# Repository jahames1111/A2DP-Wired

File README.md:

## A2DP-Wired headphones adapter

# Idea:

My parents are, well, old, so they have a lot of old wired headphones lying around their house. However, most of these are useless as their phones don't have the right kind of audio connector. I built this project to let them use all of their wired headphones with Bluetooth so they don't have to throw them away. This combines the best and easiest-to-solder chips that I could possibly find to make a device that turns these old pieces of hardware into useful music streaming tools.

Portable Bluetooth wired headphones adapter.

# Features

• ESP32-WROOM-32E: Bluetooth classic streaming

• PCM5102A DAC: audio 

• SSD1306 OLED: status screen

• 5V USB-C / LiPo: power

• SPDT Switch: Power input switching

• MIC5219 LDO: holds 3V3

• CH340C Serial: Easy USB programming

• 0805 Footprints: Hand-solder friendly

# Onboard Parts & Connectors

|Designators        |Value                    |Package  |LCSC#    |MPN                |Manufacturer             |
|-------------------|-------------------------|---------|---------|-------------------|-------------------------|
|C1                 |10uF                     |0603     |C19702   |CL10A106KP8NNNC    |Samsung Electro-Mechanics|
|C2                 |470pF                    |0603     |C22396   |CL10B471KB8NNNC    |Samsung Electro-Mechanics|
|C3                 |10uF                     |0805     |C440198  |GRM21BR61H106KE43L |muRata                   |
|C4,C5,C6,C9        |100nF                    |0603     |C1591    |CL10B104KB8NNNC    |Samsung Electro-Mechanics|
|C7,C8              |2.2uF                    |0805     |C19110   |CL21B225KAFNNNE    |Samsung Electro-Mechanics|
|C10,C11            |2.2nF                    |0603     |C16033   |CL10B222KB8NNNC    |Samsung Electro-Mechanics|
|R1,R2              |5.1k                     |0603     |C2907044 |FRC0603F5101TS     |FOJAN                    |
|R3,R4              |10k                      |0603     |C98220   |RC0603FR-0710KL    |YAGEO                    |
|R5                 |330                      |0603     |C23138   |0603WAF3300T5E     |UNI-ROYAL                |
|R6                 |2k                       |0603     |C22975   |0603WAF2001T5E     |UNI-ROYAL                |
|R7,R10             |470                      |0603     |C23179   |0603WAF4700T5E     |UNI-ROYAL                |
|R8,R9              |100k                     |0603     |C14675   |RC0603FR-07100KL   |YAGEO                    |
|R11,R12            |4.7k                     |0603     |C99782   |RC0603FR-074K7L    |YAGEO                    |
|D1                 |LED Red                  |0603     |C2286    |KT-0603R           |Hubei KENTO              |
|U1                 |ESP32-WROOM-32E-N16      |Module   |C701343  |ESP32-WROOM-32E-N16|ESPRESSIF                |
|U2                 |CH340C                   |SOP-16   |C84681   |CH340C             |WCH                      |
|U3                 |MIC5219-3.3YM5 Compatible|SOT-23-5L|C41381680|HMIC5219-3.3YM5    |HXY                      |
|U4                 |MCP73831T-2ACI/OT        |SOT-23-5 |C424093  |MCP73831T-2ACI/OT  |MICROCHIP                |
|U5                 |PCM5102APW               |TSSOP-20 |C1520792 |PCM5102APW         |TI                       |
|J1                 |USB-C Receptacle         |SMD      |C165948  |TYPE-C-31-M-12     |Hroparts                 |
|J4                 |3.5mm Audio Jack         |SMD      |C431535  |PJ-320D            |SHOU HAN                 |
|SW1,SW2            |Tactile Switch           |SMD      |C2886894 |TL3342F260QG       |E-Switch                 |
|SW3                |Slide Switch SPDT        |SMD      |C221841  |PCM12SMTR          |C&K                      |
|SW4,SW5,SW6,SW7,SW8|Tactile Switch           |THT      |C393938  |TS665CJ            |SHOU HAN                 |

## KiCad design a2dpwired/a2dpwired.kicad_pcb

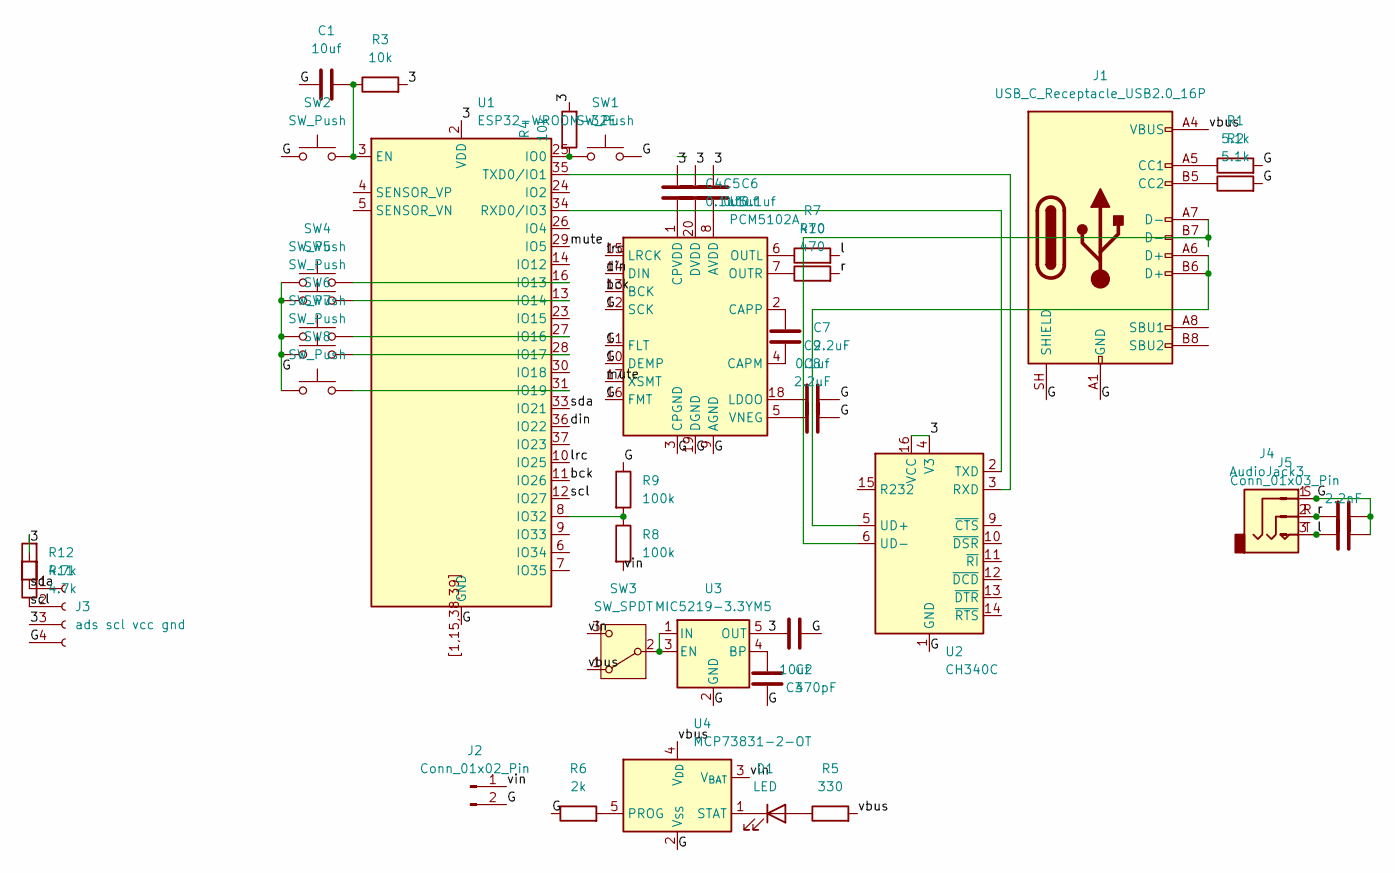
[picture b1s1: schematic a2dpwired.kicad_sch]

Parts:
C1: 10uf; C_0603_1608Metric_Pad1.08x0.95mm_HandSolder
C2: 470pF; C_0603_1608Metric_Pad1.08x0.95mm_HandSolder
C3: 10uf; C_0805_2012Metric_Pad1.18x1.45mm_HandSolder
C4, C5, C6, C9: 0.1uf; C_0603_1608Metric_Pad1.08x0.95mm_HandSolder
C7, C8: 2.2uF; C_0805_2012Metric_Pad1.18x1.45mm_HandSolder
C10, C11: 2.2nF; C_0603_1608Metric_Pad1.08x0.95mm_HandSolder
D1: LED; LED_0805_2012Metric_Pad1.15x1.40mm_HandSolder
J1: USB_C_Receptacle_USB2.0_16P; USB_C_Receptacle_HRO_TYPE-C-31-M-12
J2: Conn_01x02_Pin; PinSocket_1x02_P2.54mm_Vertical
J3: ads scl vcc gnd; PinSocket_1x04_P2.54mm_Vertical
J4: AudioJack3; Jack_3.5mm_PJ320D_Horizontal
J5: Conn_01x03_Pin; PinSocket_1x03_P2.54mm_Vertical
R1, R2: 5.1k; R_0603_1608Metric_Pad0.98x0.95mm_HandSolder
R3, R4: 10k; R_0603_1608Metric_Pad0.98x0.95mm_HandSolder
R5: 330; R_0603_1608Metric_Pad0.98x0.95mm_HandSolder
R6: 2k; R_0603_1608Metric_Pad0.98x0.95mm_HandSolder
R7, R10: 470; R_0603_1608Metric_Pad0.98x0.95mm_HandSolder
R8, R9: 100k; R_0603_1608Metric_Pad0.98x0.95mm_HandSolder
R11, R12: 4.7k; R_0603_1608Metric_Pad0.98x0.95mm_HandSolder
SW1, SW2: SW_Push; SW_SPST_TL3342
SW3: SW_SPDT; SW_SPDT_PCM12
SW4, SW5, SW6, SW7, SW8: SW_Push; SW_PUSH_6mm_H4.3mm
U1: ESP32-WROOM-32E
U2: CH340C; SOIC-16_3.9x9.9mm_P1.27mm
U3: MIC5219-3.3YM5; SOT-23-5
U4: MCP73831-2-OT; SOT-23-5
U5: PCM5102A; TSSOP-20_4.4x6.5mm_P0.65mm

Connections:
/3: C3.2, C4.1, C5.1, C6.1, J3.3, R3.2, R4.2, R11.2, R12.2, U1.2 (VDD), U2.4 (V3), U2.16 (VCC), U3.5 (OUT)
/G: C1.1, C2.2, C3.1, C8.2, C9.2, C10.2, C11.2, J1.A1 (GND), J1.A12 (GND), J1.B1 (GND), J1.B12 (GND), J1.SH (SHIELD), J2.2, J3.4, J4.S, J5.1, R1.2, R2.2, R6.1, R9.1, SW1.2, SW2.1, SW4.1, SW5.1, SW6.1, SW7.1, SW8.1, U1.1 (GND), U1.15 (GND), U1.38 (GND), U1.39 (GND), U1.[1,15,38,39] (GND), U2.1 (GND), U3.2 (GND), U4.2 (V_{SS}), U5.3 (CPGND), U5.9 (AGND), U5.10 (DEMP), U5.11 (FLT), U5.12 (SCK), U5.16 (FMT), U5.19 (DGND)
/bck: U1.11 (IO26), U5.13 (BCK)
/din: U1.36 (IO22), U5.14 (DIN)
/l: C11.1, J4.T, J5.3, R7.2
/lrc: U1.10 (IO25), U5.15 (LRCK)
/mute: U1.29 (IO5), U5.17 (XSMT)
/r: C10.1, J4.R, J5.2, R10.2
/scl: J3.2, R11.1, U1.12 (IO27)
/sda: J3.1, R12.1, U1.33 (IO21)
/vbus: J1.A4 (VBUS), J1.A9 (VBUS), J1.B4 (VBUS), J1.B9 (VBUS), R5.2, SW3.1 (A), U4.4 (V_{DD})
/vin: J2.1, R8.2, SW3.3 (C), U4.3 (V_{BAT})
unnamed: D1.2 (A), R5.1
unnamed: D1.1 (K), U4.1 (STAT)
unnamed: J1.A5 (CC1), R1.1
unnamed: J1.B5 (CC2), R2.1
unnamed: SW3.2 (B), U3.1 (IN), U3.3 (EN)
unnamed: C1.2, R3.1, SW2.2, U1.3 (EN)
unnamed: R4.1, SW1.1, U1.25 (IO0)
unnamed: SW4.2, U1.16 (IO13)
unnamed: SW5.2, U1.13 (IO14)
unnamed: SW6.2, U1.27 (IO16)
unnamed: SW7.2, U1.28 (IO17)
unnamed: SW8.2, U1.31 (IO19)
unnamed: R8.1, R9.2, U1.8 (IO32)
unnamed: U1.34 (RXD0/IO3), U2.2 (TXD)
unnamed: U1.35 (TXD0/IO1), U2.3 (RXD)
unnamed: J1.A6 (D+), J1.B6 (D+), U2.5 (UD+)
unnamed: J1.A7 (D-), J1.B7 (D-), U2.6 (UD-)
unnamed: C2.1, U3.4 (BP)
unnamed: R6.2, U4.5 (PROG)
unnamed: C6.2, U5.8 (AVDD)
unnamed: C7.2, U5.4 (CAPM)
unnamed: C7.1, U5.2 (CAPP)
unnamed: C4.2, U5.1 (CPVDD)
unnamed: C5.2, U5.20 (DVDD)
unnamed: C9.1, U5.18 (LDOO)
unnamed: R7.1, U5.6 (OUTL)
unnamed: R10.1, U5.7 (OUTR)
unnamed: C8.1, U5.5 (VNEG)

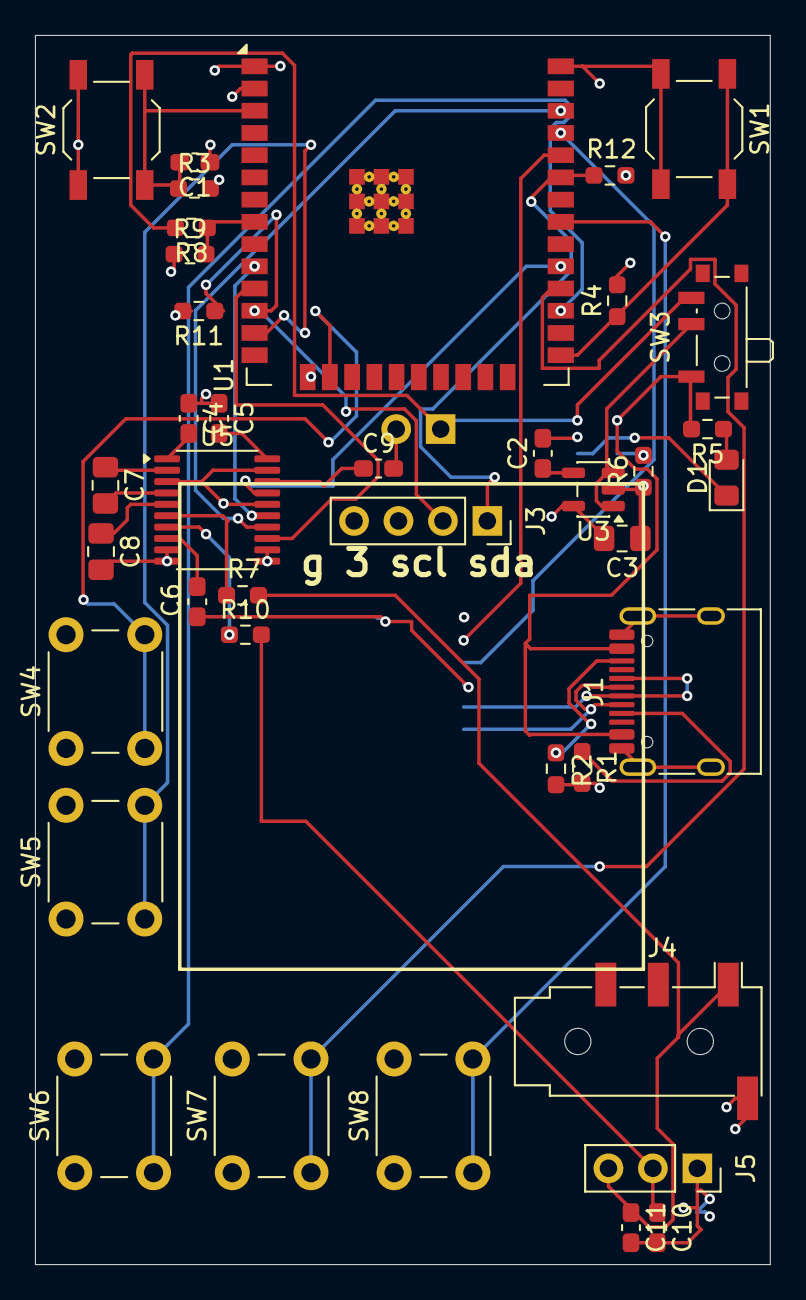
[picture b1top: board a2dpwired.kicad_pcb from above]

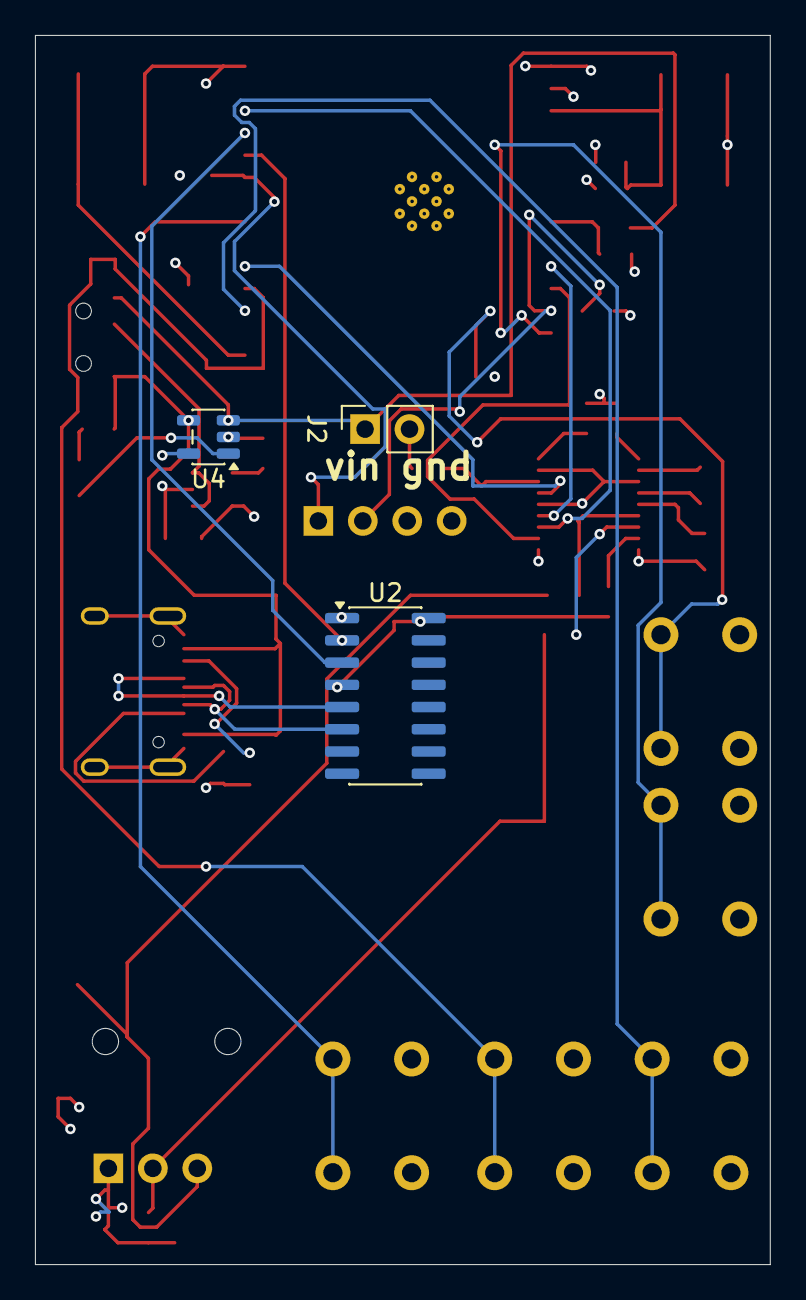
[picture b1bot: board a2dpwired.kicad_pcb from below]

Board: 4 copper layers, 42.0 x 70.2 mm, 42 parts (3 on the bottom side), 40 nets.

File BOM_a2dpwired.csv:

References,Value,Qty,Description
"C1,C3",10uF,2,Capacitor
C2,470pF,1,Capacitor
"C4,C5,C6,C9",0.1uF,4,Capacitor
"C7,C8",2.2uF,2,Capacitor
"C10,C11",2.2nF,2,Capacitor
"R1,R2",5.1k,2,Resistor
"R3,R4",10k,2,Resistor
R5,330,1,Resistor
R6,2k,1,Resistor
"R7,R10",470,2,Resistor
"R8,R9",100k,2,Resistor
"R11,R12",4.7k,2,Resistor
D1,LED,1,LED
J1,USB_C_Receptacle_USB2.0_16P,1,USB Connector
J2,Conn_01x02_Pin,1,Battery Connector
J3,Conn_01x04 Socket (ADS/SCL/VCC/GND),1,I2C Header
J4,AudioJack3,1,3.5mm Audio Jack
J5,Conn_01x03_Pin,1,Audio Header
"SW1,SW2",SW_Push SMD,2,Push Button
SW3,SW_SPDT,1,Power Switch
"SW4,SW5,SW6,SW7,SW8",SW_Push THT,5,Push Button
U1,ESP32-WROOM-32E,1,MCU Module
U2,CH340C,1,USB-UART
U3,MIC5219-3.3YM5,1,3.3V LDO
U4,MCP73831-2-OT,1,LiPo Charger
U5,PCM5102A,1,I2S Audio DAC
